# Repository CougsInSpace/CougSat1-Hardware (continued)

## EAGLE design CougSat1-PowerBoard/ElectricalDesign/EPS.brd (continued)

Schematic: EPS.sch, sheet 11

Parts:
C16, C26, C90: 10µF 10%; 1608
C18, C19, C21, C23, C27, C31, C83, C86, C87: 100nF 10%; 1608
RN6, RN7, RN8, RN9, RN10, RN11, RN13, RN14, RN17, RN20, RN21, RN22, RN23: 5kΩ 0.1%; 1616
TP4, TP27, TP28, TP30: TEST_POINT-SMD-C-1.25; SMD-C-1.25
U8, U11, U42: AD7689; QFN-20-4040

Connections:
3.3V: C18.1, C31.1, C87.1, RN14.2 (B1), U8.15 (VIO), U11.15 (VIO), U42.15 (VIO); also elsewhere on the board
ADC_3.3V: RN14.3 (B2), RN14.4 (A2), U8.6 (IN4)
ADC_EJECT_TIMER_BUF: RN13.3 (B2), RN13.4 (A2), U11.19 (IN3)
ADC_PV_IN-0A: RN23.3 (B2), RN23.4 (A2), U42.16 (IN0)
ADC_PV_IN-0B: RN22.3 (B2), RN22.4 (A2), U42.17 (IN1)
ADC_PV_IN-1A: RN21.3 (B2), RN21.4 (A2), U42.18 (IN2)
ADC_PV_IN-1B: RN20.3 (B2), RN20.4 (A2), U42.19 (IN3)
ADC_PV_IN-2A: RN8.3 (B2), RN8.4 (A2), U8.18 (IN2)
ADC_PV_IN-2B: RN9.3 (B2), RN9.4 (A2), U8.19 (IN3)
ADC_PV_IN-3A: RN7.3 (B2), RN7.4 (A2), U8.17 (IN1)
ADC_PV_IN-3B: RN6.3 (B2), RN6.4 (A2), U8.16 (IN0)
ADC_REF-0: C16.1, TP30.1, U8.2 (REF)
ADC_REF-1: C90.1, TP4.1, U42.2 (REF)
ADC_REF-2: C26.1, TP27.1, U11.2 (REF)
ADC_REFIN-0: C21.1, U8.3 (REFIN)
ADC_REFIN-1: C83.1, U42.3 (REFIN)
ADC_REFIN-2: C23.1, U11.3 (REFIN)
ADC_SEL-0: U8.11 (CNV); also elsewhere on the board
ADC_SEL-1: U42.11 (CNV); also elsewhere on the board
ADC_SEL-2: U11.11 (CNV); also elsewhere on the board
ADC_UMB_IN: RN10.3 (B2), RN10.4 (A2), U11.8 (IN6)
ADC_VBATT-A: RN17.3 (B2), RN17.4 (A2), U42.9 (IN7)
ADC_VBATT-B: RN11.3 (B2), RN11.4 (A2), U11.9 (IN7)
AGND: C16.2, C21.2, C23.2, C26.2, C83.2, C90.2, RN6.1 (A1), RN7.1 (A1), RN8.1 (A1), RN9.1 (A1), RN10.1 (A1), RN11.1 (A1), RN13.1 (A1), RN14.1 (A1), RN17.1 (A1), RN20.1 (A1), RN21.1 (A1), RN22.1 (A1), RN23.1 (A1), TP28.1, U8.9 (IN7), U8.10 (COM), U11.10 (COM), U42.10 (COM); also elsewhere on the board
AVDD: C19.1, C27.1, C86.1, U8.1 (VDD), U8.20 (VDD), U11.1 (VDD), U11.20 (VDD), U42.1 (VDD), U42.20 (VDD); also elsewhere on the board
DEPLOY_SENSE-0: U42.8 (IN6); also elsewhere on the board
DGND: C18.2, C19.2, C27.2, C31.2, C86.2, C87.2, U8.4 (GND), U8.5 (GND), U8.PAD (GND), U11.4 (GND), U11.5 (GND), U11.16 (IN0), U11.17 (IN1), U11.18 (IN2), U11.PAD (GND), U42.4 (GND), U42.5 (GND), U42.PAD (GND); also elsewhere on the board
EJECT_TIMER_BUF: RN13.2 (B1); also elsewhere on the board
I_3.3V_IN: U8.8 (IN6); also elsewhere on the board
I_3.3V_OUT: U8.7 (IN5); also elsewhere on the board
I_BATT_IN-A: U42.7 (IN5); also elsewhere on the board
I_BATT_IN-B: U11.6 (IN4); also elsewhere on the board
I_BATT_OUT-A: U42.6 (IN4); also elsewhere on the board
I_BATT_OUT-B: U11.7 (IN5); also elsewhere on the board
PV_IN-0A: RN23.2 (B1); also elsewhere on the board
PV_IN-0B: RN22.2 (B1); also elsewhere on the board
PV_IN-1A: RN21.2 (B1); also elsewhere on the board
PV_IN-1B: RN20.2 (B1); also elsewhere on the board
PV_IN-2A: RN8.2 (B1); also elsewhere on the board
PV_IN-2B: RN9.2 (B1); also elsewhere on the board
PV_IN-3A: RN7.2 (B1); also elsewhere on the board
PV_IN-3B: RN6.2 (B1); also elsewhere on the board
SPI_MISO: U8.14 (SDO), U11.14 (SDO), U42.14 (SDO); also elsewhere on the board
SPI_MOSI: U8.12 (DIN), U11.12 (DIN), U42.12 (DIN); also elsewhere on the board
SPI_SCK: U8.13 (SCK), U11.13 (SCK), U42.13 (SCK); also elsewhere on the board
UMB_IN: RN10.2 (B1); also elsewhere on the board
VBATT-A: RN17.2 (B1); also elsewhere on the board
VBATT-B: RN11.2 (B1); also elsewhere on the board

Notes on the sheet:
CAD Note: Decoupling
0-2.5V=38µV/LSB 76µV/LSB with -6dB attenuation
4A3>
4A5>
4B5>
4B3>
4A1>
4C5>
5B2>
5B5>
5B6>
5B1>
6B6>
6C5>
6B3>
6D2>
<10A1
10A1>
<10B1
<10D1

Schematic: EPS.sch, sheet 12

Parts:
C6, C15, C57, C69, C93: 1µF 10%; 1608
C7, C8, C11, C13, C17, C22, C37, C55, C59, C65, C72, C92, C96: 100nF 10%; 1608
C10, C14, C61, C75, C104: 10µF 10%; 1608
C40: 4.7µF 10%; 4028-POL
FB1: 1.5kΩ @ 100MHz; 1608
RN4, RN12: 10kΩ 5%; 3264
RT3, RT4, RT7, RT10: 10kΩ 5%; 1608
TP1, TP9, TP10, TP20, TP22, TP31, TP33, TP36, TP38: TEST_POINT-SMD-C-1.25; SMD-C-1.25
U2, U9, U26, U35, U49: AD7291; QFN-20-4040
U4, U7: AD8515; SOT23-5

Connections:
3.3V: C7.1, C22.1, C55.1, C65.1, C92.1, FB1.1, U2.11 (AS0), U2.13 (AS1), U2.16 (VDRIVE), U2.17 (!PD!/!RST), U9.16 (VDRIVE), U9.17 (!PD!/!RST), U26.16 (VDRIVE), U26.17 (!PD!/!RST), U35.16 (VDRIVE), U35.17 (!PD!/!RST), U49.11 (AS0), U49.16 (VDRIVE), U49.17 (!PD!/!RST); also elsewhere on the board
ADC_DCAP-3: C93.1, U49.8 (DCAP)
ADC_DCAP-4: C69.1, U35.8 (DCAP)
ADC_DCAP-5: C57.1, U26.8 (DCAP)
ADC_DCAP-6: C15.1, U9.8 (DCAP)
ADC_DCAP-7: C6.1, U2.8 (DCAP)
ADC_REF-3: C104.1, TP1.1, U49.7 (VREF)
ADC_REF-4: C75.1, TP9.1, U35.7 (VREF)
ADC_REF-5: C61.1, TP10.1, U26.7 (VREF)
ADC_REF-6: C14.1, TP33.1, U7.3 (IN+), U9.7 (VREF)
ADC_REF-7: C10.1, TP38.1, U2.7 (VREF), U4.3 (IN+)
AGND: C8.2, C10.2, C11.2, C13.2, C14.2, C17.2, C37.2, C40.C, RT3.1, RT4.1, RT7.1, RT10.1, TP20.1, U2.6 (AGND), U4.2 (V-), U7.2 (V-), U9.6 (AGND); also elsewhere on the board
AVDD: C8.1, C11.1, C13.1, C17.1, C37.1, C40.A, C59.1, C72.1, C96.1, FB1.2, TP22.1, U2.10 (VDD), U4.5 (V+), U7.5 (V+), U9.10 (VDD), U26.10 (VDD), U35.10 (VDD), U49.10 (VDD); also elsewhere on the board
AVREF-0: RN12.5 (C), RN12.10 (C), TP31.1, U7.1 (OUT), U7.4 (IN-)
AVREF-1: RN4.5 (C), RN4.10 (C), TP36.1, U4.1 (OUT), U4.4 (IN-)
DEPLOY_SENSE-1: U2.18 (IN0); also elsewhere on the board
DGND: C6.2, C7.2, C15.2, C22.2, C55.2, C57.2, C65.2, C69.2, C92.2, C93.2, U2.9 (DGND), U2.PAD (DGND), U9.9 (DGND), U9.11 (AS0), U9.PAD (DGND), U26.4 (IN6), U26.9 (DGND), U26.11 (AS0), U26.13 (AS1), U26.19 (IN1), U26.PAD (DGND), U35.9 (DGND), U35.13 (AS1), U35.PAD (DGND), U49.9 (DGND), U49.13 (AS1), U49.PAD (DGND); also elsewhere on the board
I2C_SCL: U2.15 (SCL), U9.15 (SCL), U26.15 (SCL), U35.15 (SCL), U49.15 (SCL); also elsewhere on the board
I2C_SDA: U2.14 (SDA), U9.14 (SDA), U26.14 (SDA), U35.14 (SDA), U49.14 (SDA); also elsewhere on the board
I_3.3V-0: U49.5 (IN7); also elsewhere on the board
I_3.3V-1: U49.4 (IN6); also elsewhere on the board
I_3.3V-2: U49.3 (IN5); also elsewhere on the board
I_3.3V-3: U49.2 (IN4); also elsewhere on the board
I_3.3V-4: U49.1 (IN3); also elsewhere on the board
I_3.3V-5: U49.20 (IN2); also elsewhere on the board
I_3.3V-6: U49.19 (IN1); also elsewhere on the board
I_3.3V-7: U49.18 (IN0); also elsewhere on the board
I_3.3V-8: U35.5 (IN7); also elsewhere on the board
I_3.3V-9: U35.4 (IN6); also elsewhere on the board
I_3.3V-10: U35.3 (IN5); also elsewhere on the board
I_3.3V-11: U35.2 (IN4); also elsewhere on the board
I_3.3V-12: U35.1 (IN3); also elsewhere on the board
I_3.3V-PV: U2.5 (IN7); also elsewhere on the board
I_BATT-0: U35.20 (IN2); also elsewhere on the board
I_BATT-1: U35.19 (IN1); also elsewhere on the board
I_BATT-2: U35.18 (IN0); also elsewhere on the board
I_BATT-3: U26.3 (IN5); also elsewhere on the board
I_BATT-4: U26.2 (IN4); also elsewhere on the board
I_BATT-5: U26.1 (IN3); also elsewhere on the board
I_BATT-6: U26.20 (IN2); also elsewhere on the board
I_BH-0: U26.18 (IN0); also elsewhere on the board
I_BH-1: U9.18 (IN0); also elsewhere on the board
I_DP-0: U9.3 (IN5); also elsewhere on the board
I_DP-1: U2.20 (IN2); also elsewhere on the board
PGND: C59.2, C61.2, C72.2, C75.2, C96.2, C104.2, U26.5 (IN7), U26.6 (AGND), U35.6 (AGND), U49.6 (AGND); also elsewhere on the board
TEMP-BATT-A: RN4.6 (5), U2.3 (IN5); also elsewhere on the board
TEMP-BATT-B: RN4.3, U2.2 (IN4); also elsewhere on the board
TEMP-IN_SW-0: RN4.8 (7), U2.1 (IN3); also elsewhere on the board
TEMP-IN_SW-1: RN12.6 (5), U9.5 (IN7); also elsewhere on the board
TEMP-OUT_SW-0: RN12.1, U9.19 (IN1); also elsewhere on the board
TEMP-OUT_SW-1: RN4.4, U2.4 (IN6); also elsewhere on the board
TEMP-PCB-0: RN4.9 (8), RT4.2, U2.19 (IN1)
TEMP-PCB-1: RN12.8 (7), RT7.2, U9.2 (IN4)
TEMP-PCB-2: RN12.2, RT10.2, U9.1 (IN3)
TEMP-PCB-3: RN12.4, RT3.2, U9.4 (IN6)
TEMP-REG: RN12.9 (8), U9.20 (IN2); also elsewhere on the board

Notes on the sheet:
CAD Note: Decoupling
Addr=0x2C (7b)
Addr=0x2E (7b)
Addr=0x2F (7b)
Addr=0x2B (7b)
Addr=0x20 (7b)
CAD Note: Place at various locations around the PCB
0-2.5V=610µV/LSB
Note: Inputs PGND Referenced
<10B1
<10B1>
12A4>
7A2>
7A4>
7A6>
7B2>
7B4>
7B6>
7C2>
7C4>
7C6>
7D2>
7D4>
7D6>
8A2>
8A4>
8A6>
8B2>
8B4>
8B6>
8C2>
8C4>
8C6>
8D6>
8D4>
8D2>
4D6>
4D3>
5B2>
5B5>

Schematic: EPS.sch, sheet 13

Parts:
J6: CougSat Card; CARD-FULL-OPEN+X
LOGO1: SIGNATUREBRADLEY; SIGN-BRADLEY
LOGO2: Satellite 16mm; CIS-SATELLITE-16

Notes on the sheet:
PV 0,1
PV 2,3
PV 4,5
PV 6,7
Battery 0
Battery 1
PMIC SWD
Umb
RBF Pin
RBF Switch
Deploy ables

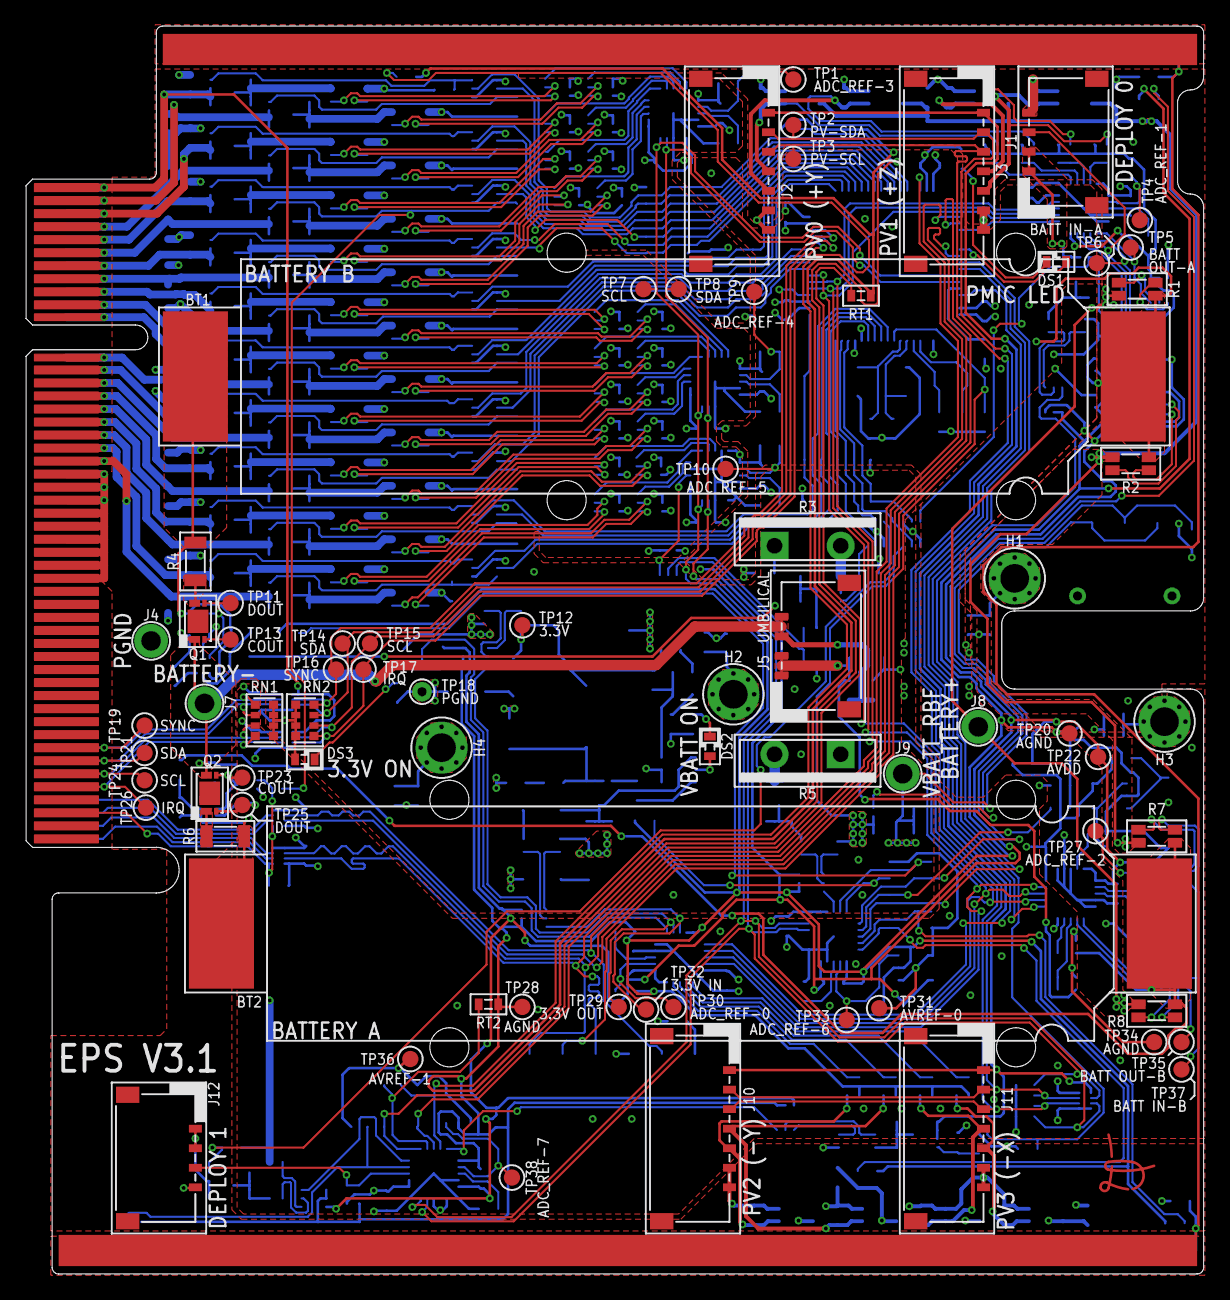
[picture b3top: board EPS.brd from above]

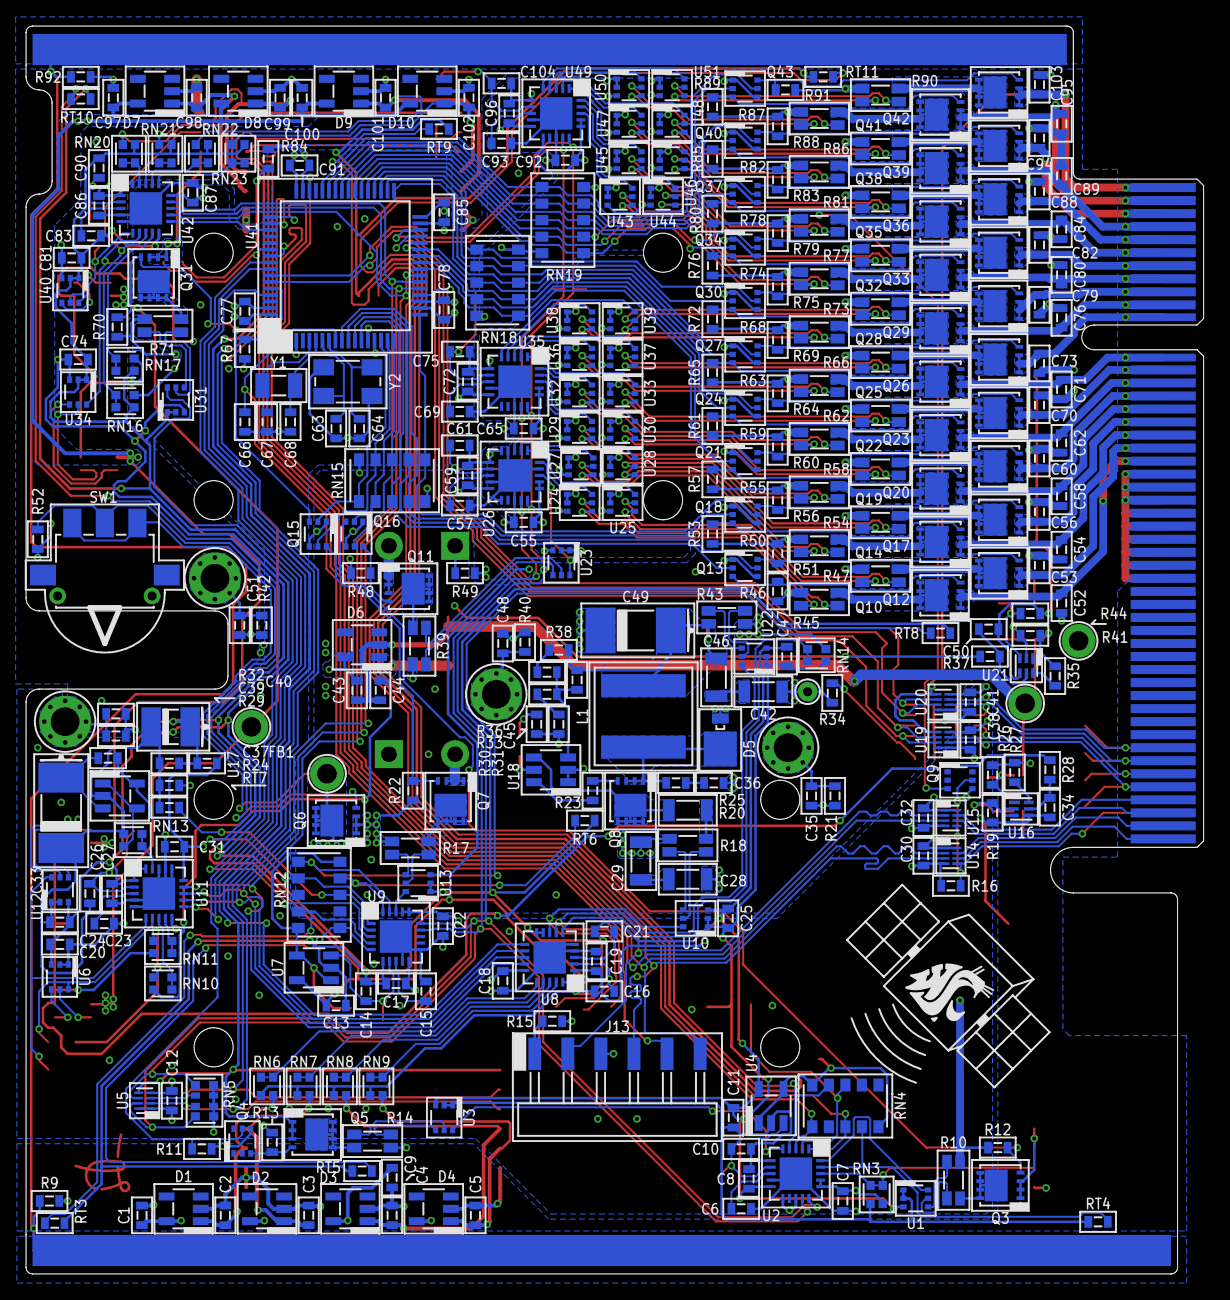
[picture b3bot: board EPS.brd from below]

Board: 4 copper layers, 90.4 x 95.8 mm, 401 parts (327 on the bottom side), 328 nets.

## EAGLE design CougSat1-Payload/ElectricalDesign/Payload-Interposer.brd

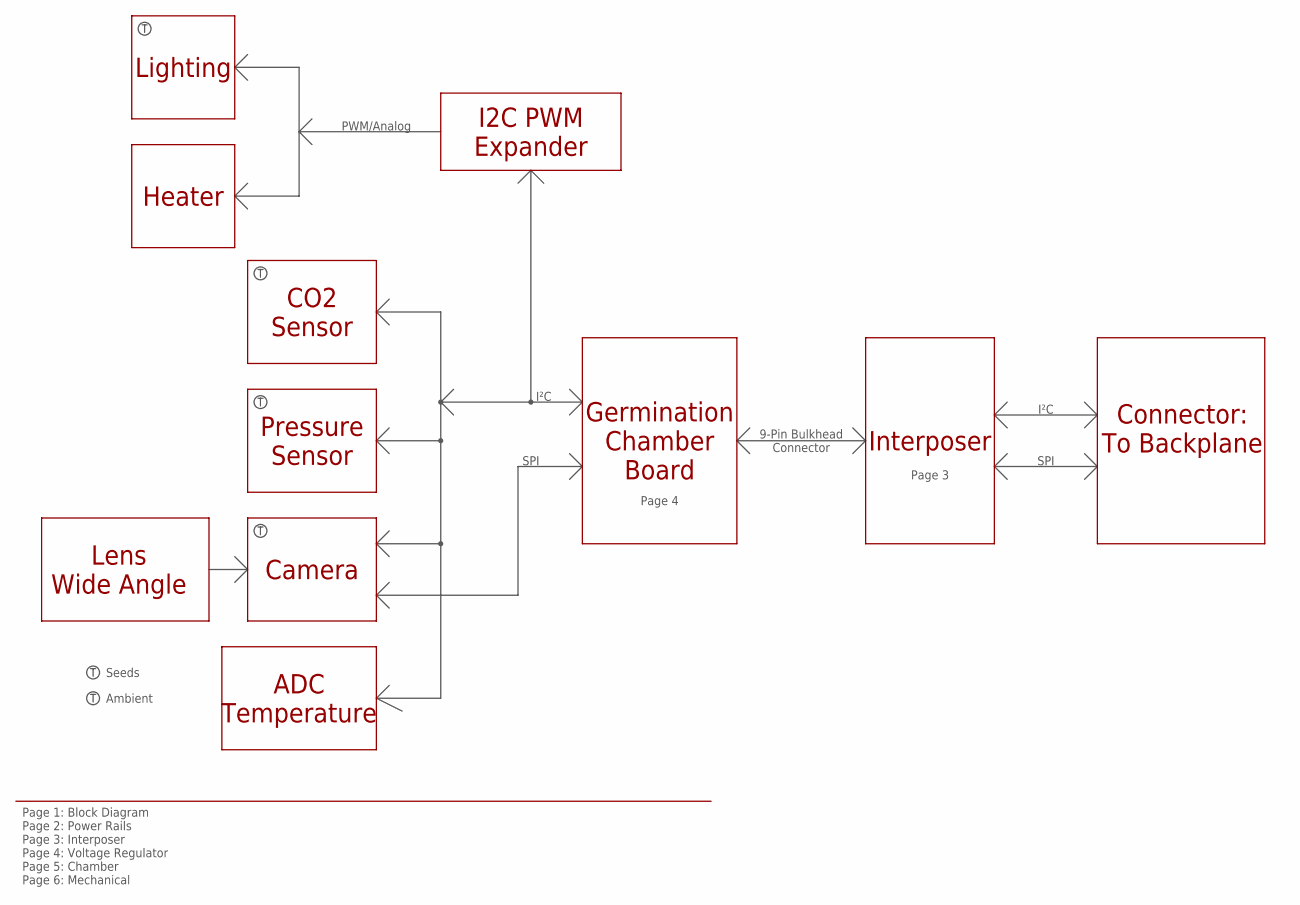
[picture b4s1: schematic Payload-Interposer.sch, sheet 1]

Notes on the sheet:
Connector: To Backplane
Camera
Lighting
Lens Wide Angle
Pressure Sensor
ADC Temperature
I²C
SPI
Seeds
Page 1: Block Diagram Page 2: Power Rails Page 3: Interposer Page 4: Voltage Regulator Page 5: Chamber Page 6: Mechanical
Heater
Ambient
CO2 Sensor
Interposer
Germination Chamber Board
9-Pin Bulkhead Connector
I2C PWM Expander
PWM/Analog
Page 3
Page 4

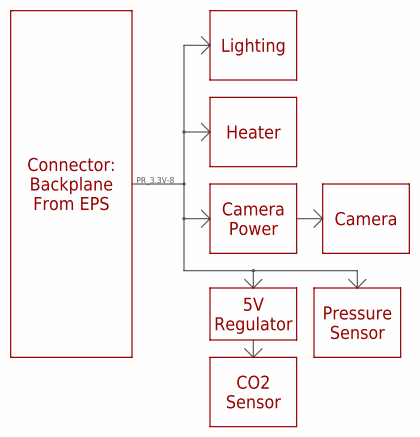
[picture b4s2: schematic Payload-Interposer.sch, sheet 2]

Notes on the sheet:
Connector: Backplane From EPS
Camera Power
Heater
CO2 Sensor
Pressure Sensor
PR_3.3V-8
Lighting
5V Regulator
Camera

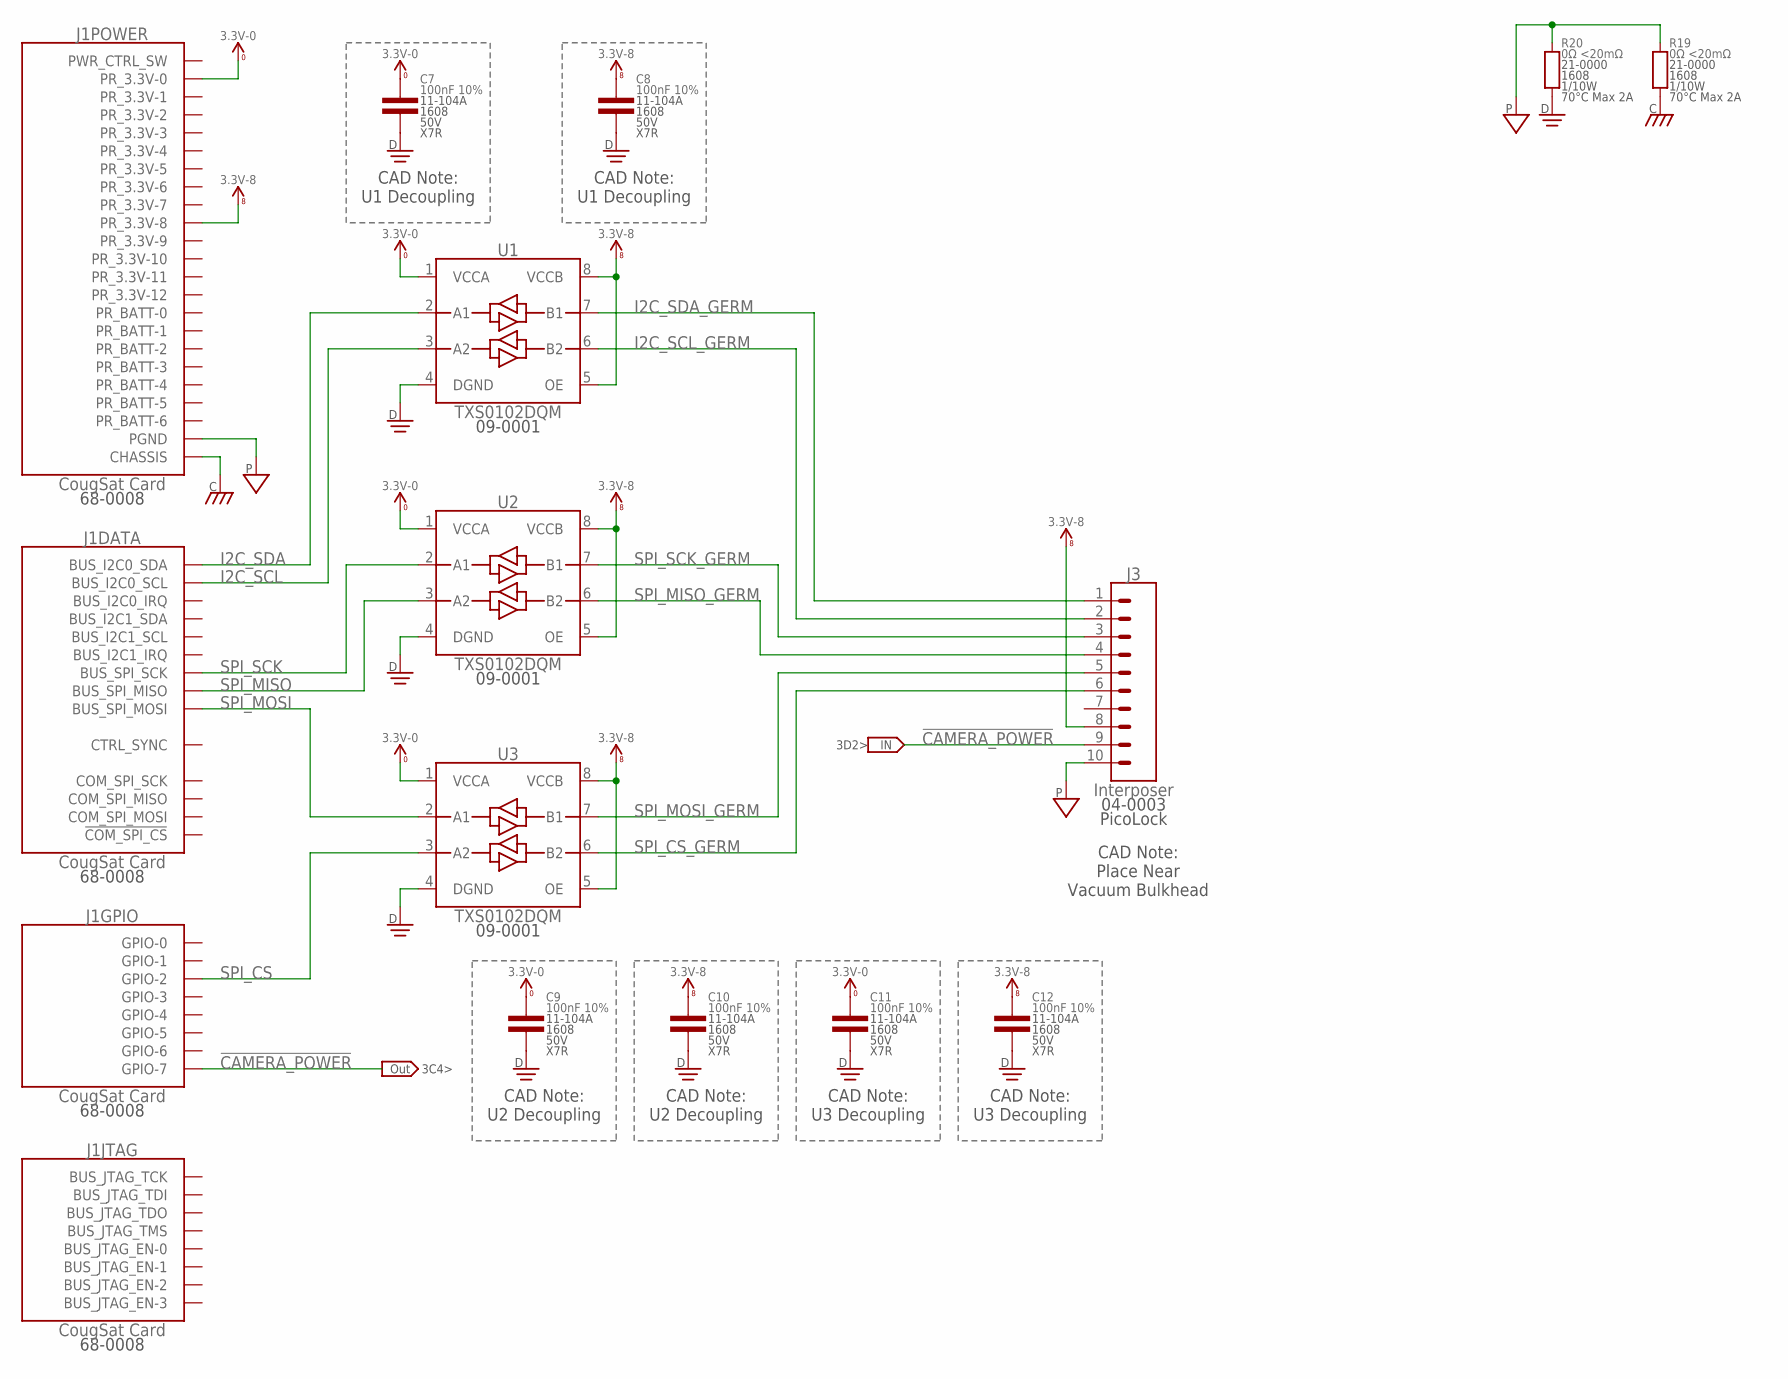
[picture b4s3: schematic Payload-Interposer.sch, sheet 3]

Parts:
C7, C8, C9, C10, C11, C12: 100nF 10%; 1608
J1: CougSat Card; CARD-FULL-OPEN+X
J3: Interposer; PICOLOCK1.5-10
R19, R20: 0Ω <20mΩ; 1608
U1, U2, U3: TXS0102DQM; X2SON-8

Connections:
3.3V_0: C7.1, C9.1, C11.1, J1.A1 (PR_3.3V-0), J1.B1 (PR_3.3V-0), U1.1 (VCCA), U2.1 (VCCA), U3.1 (VCCA)
3.3V_8: C8.1, C10.1, C12.1, J1.A9 (PR_3.3V-8), J1.B9 (PR_3.3V-8), J3.8, U1.5 (OE), U1.8 (VCCB), U2.5 (OE), U2.8 (VCCB), U3.5 (OE), U3.8 (VCCB); also elsewhere on the board
!CAMERA_POWER: J1.B41 (GPIO-7), J3.9; also elsewhere on the board
CHASSIS: J1.CHASSIS@1 (CHASSIS), J1.CHASSIS@2 (CHASSIS), J1.CHASSIS@3 (CHASSIS), J1.CHASSIS@4 (CHASSIS), R19.1; also elsewhere on the board
DGND: C7.2, C8.2, C9.2, C10.2, C11.2, C12.2, R20.1, U1.4 (DGND), U2.4 (DGND), U3.4 (DGND); also elsewhere on the board
I2C_SCL: J1.A44 (BUS_I2C0_SCL), J1.B44 (BUS_I2C0_SCL), U1.3 (A2)
I2C_SCL_GERM: J3.2, U1.6 (B2); also elsewhere on the board
I2C_SDA: J1.A43 (BUS_I2C0_SDA), J1.B43 (BUS_I2C0_SDA), U1.2 (A1)
I2C_SDA_GERM: J3.1, U1.7 (B1); also elsewhere on the board
PGND: J1.A21 (PGND), J1.A22 (PGND), J1.A23 (PGND), J1.B21 (PGND), J1.B22 (PGND), J1.B23 (PGND), J1.B24 (PGND), J1.B25 (PGND), J1.B26 (PGND), J1.B27 (PGND), J1.B28 (PGND), J1.B29 (PGND), J3.10, R19.2, R20.2; also elsewhere on the board
PR_3.3V-1: J1.A2 (PR_3.3V-1), J1.B2 (PR_3.3V-1)
PR_3.3V-2: J1.A3 (PR_3.3V-2), J1.B3 (PR_3.3V-2)
PR_3.3V-3: J1.A4 (PR_3.3V-3), J1.B4 (PR_3.3V-3)
PR_3.3V-4: J1.A5 (PR_3.3V-4), J1.B5 (PR_3.3V-4)
PR_3.3V-5: J1.A6 (PR_3.3V-5), J1.B6 (PR_3.3V-5)
PR_3.3V-6: J1.A7 (PR_3.3V-6), J1.B7 (PR_3.3V-6)
PR_3.3V-7: J1.A8 (PR_3.3V-7), J1.B8 (PR_3.3V-7)
PR_3.3V-9: J1.A10 (PR_3.3V-9), J1.B10 (PR_3.3V-9)
PR_3.3V-10: J1.A11 (PR_3.3V-10), J1.B11 (PR_3.3V-10)
PR_3.3V-11: J1.A12 (PR_3.3V-11), J1.B12 (PR_3.3V-11)
PR_3.3V-12: J1.A13 (PR_3.3V-12), J1.B13 (PR_3.3V-12)
PR_BATT-0: J1.A14 (PR_BATT-0), J1.B14 (PR_BATT-0)
PR_BATT-1: J1.A15 (PR_BATT-1), J1.B15 (PR_BATT-1)
PR_BATT-2: J1.A16 (PR_BATT-2), J1.B16 (PR_BATT-2)
PR_BATT-3: J1.A17 (PR_BATT-3), J1.B17 (PR_BATT-3)
PR_BATT-4: J1.A18 (PR_BATT-4), J1.B18 (PR_BATT-4)
PR_BATT-5: J1.A19 (PR_BATT-5), J1.B19 (PR_BATT-5)
PR_BATT-6: J1.A20 (PR_BATT-6), J1.B20 (PR_BATT-6)
SPI_CS: J1.A26 (GPIO-2), U3.3 (A2)
SPI_CS_GERM: J3.6, U3.6 (B2); also elsewhere on the board
SPI_MISO: J1.A38 (BUS_SPI_MISO), J1.B38 (BUS_SPI_MISO), U2.3 (A2)
SPI_MISO_GERM: J3.4, U2.6 (B2); also elsewhere on the board
SPI_MOSI: J1.A39 (BUS_SPI_MOSI), J1.B39 (BUS_SPI_MOSI), U3.2 (A1)
SPI_MOSI_GERM: J3.5, U3.7 (B1); also elsewhere on the board
SPI_SCK: J1.A37 (BUS_SPI_SCK), J1.B37 (BUS_SPI_SCK), U2.2 (A1)
SPI_SCK_GERM: J3.3, U2.7 (B1); also elsewhere on the board

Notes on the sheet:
CAD Note: Place Near Vacuum Bulkhead
CAD Note: U1 Decoupling
CAD Note: U2 Decoupling
CAD Note: U3 Decoupling
3C4>
3D2>

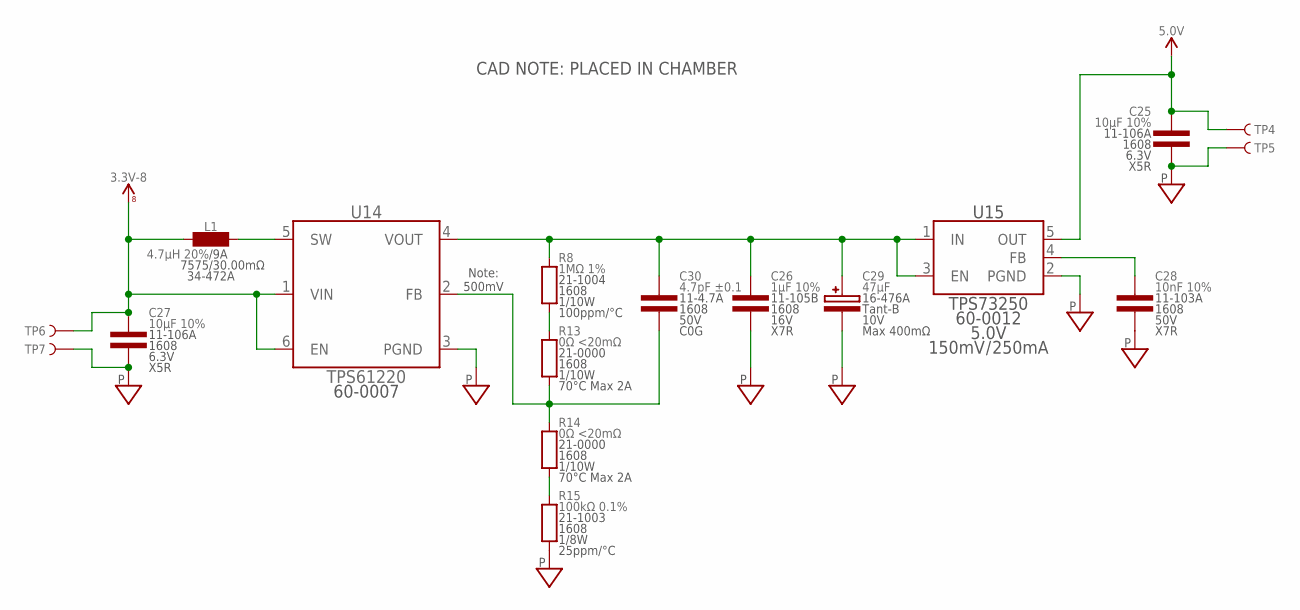
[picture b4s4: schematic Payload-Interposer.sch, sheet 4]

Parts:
C25, C27: 10µF 10%; 1608
C26: 1µF 10%; 1608
C28: 10nF 10%; 1608
C29: 47µF; 4028-POL
C30: 4.7pF ±0.1; 1608
L1: 4.7µH 20%; 7575
R8: 1MΩ 1%; 1608
R13, R14: 0Ω <20mΩ; 1608
R15: 100kΩ 0.1%; 1608
TP4, TP5, TP6, TP7: TEST_POINT-THT-1.0; THT-1.0
U14: TPS61220; SOT363
U15: TPS73250; SOT23-5

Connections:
3.3V_8: C27.1, L1.1, TP6.1, U14.1 (VIN), U14.6 (EN); also elsewhere on the board
5.0V: C25.1, TP4.1, U15.5 (OUT); also elsewhere on the board
BOOST_FB: C30.2, R13.1, R14.2, U14.2 (FB)
BOOST_FB-HIGH: R8.1, R13.2
BOOST_FB-LOW: R14.1, R15.2
BOOST_IN: L1.2, U14.5 (SW)
BOOST_OUT: C26.1, C29.A, C30.1, R8.2, U14.4 (VOUT), U15.1 (IN), U15.3 (EN)
PGND: C25.2, C26.2, C27.2, C28.2, C29.C, R15.1, TP5.1, TP7.1, U14.3 (PGND), U15.2 (PGND); also elsewhere on the board
REG_FB: C28.1, U15.4 (FB)

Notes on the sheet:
Note: 500mV
CAD NOTE: PLACED IN CHAMBER

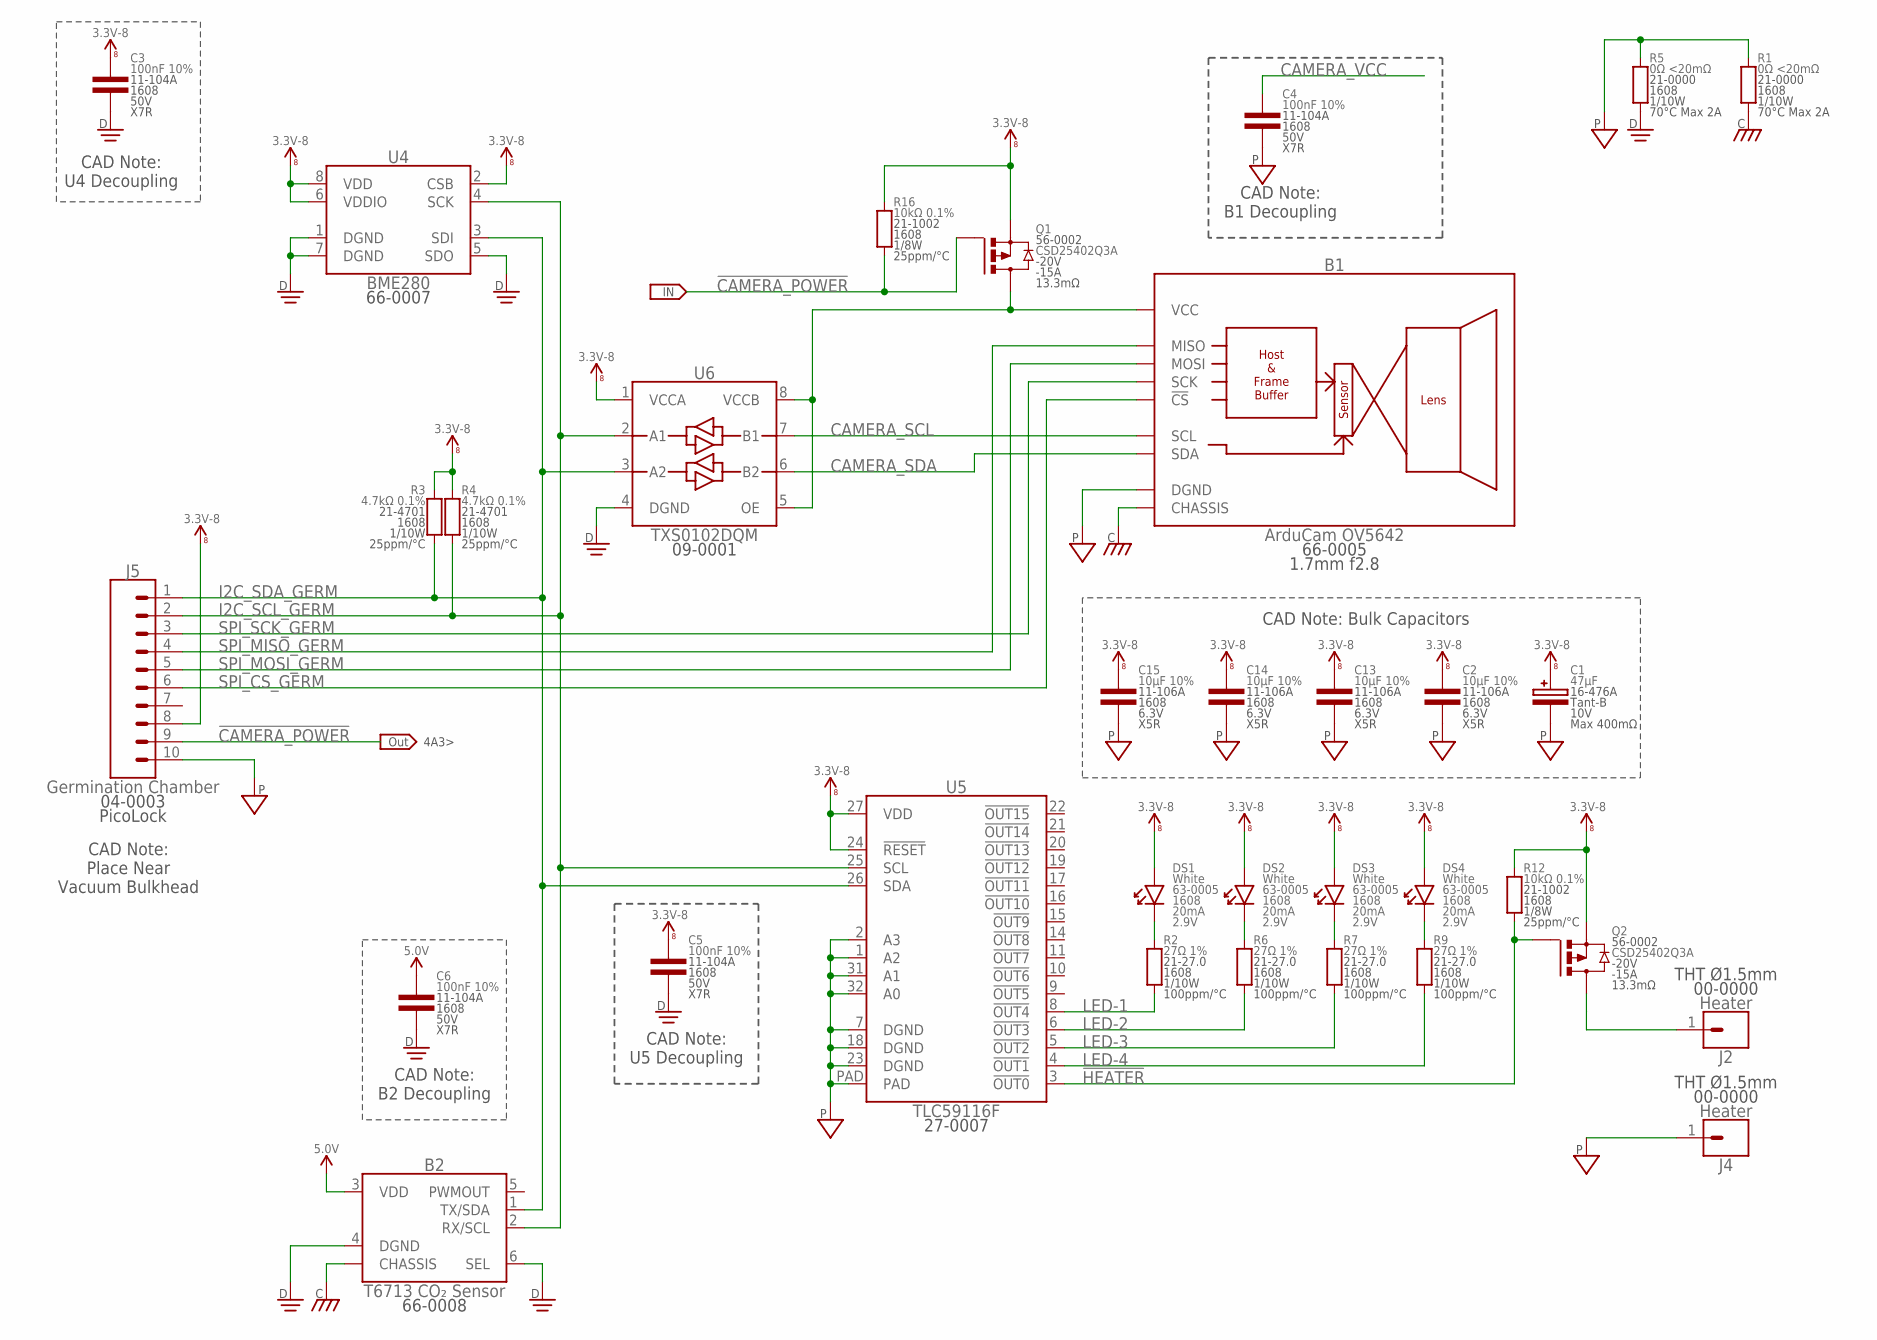
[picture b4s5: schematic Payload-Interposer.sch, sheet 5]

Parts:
B1: ArduCam OV5642; ARDUCAM
B2: T6713 CO₂ Sensor; T6713
C1: 47µF; 4028-POL
C2, C13, C14, C15: 10µF 10%; 1608
C3, C4, C5, C6: 100nF 10%; 1608
DS1, DS2, DS3, DS4: White; 1608-POL
J2, J4: Heater; THT-1.5
J5: Germination Chamber; PICOLOCK1.5-10
Q1, Q2: CSD25402Q3A; SON-3333
R1, R5: 0Ω <20mΩ; 1608
R2, R6, R7, R9: 27Ω 1%; 1608
R3, R4: 4.7kΩ 0.1%; 1608
R12, R16: 10kΩ 0.1%; 1608
U4: BME280
U5: TLC59116F; QFN-32-5050
U6: TXS0102DQM; X2SON-8

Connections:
3.3V_8: C1.A, C2.1, C3.1, C5.1, C13.1, C14.1, C15.1, DS1.A, DS2.A, DS3.A, DS4.A, J5.8, Q1.5 (S), Q1.6 (S), Q1.7 (S), Q1.8 (S), Q1.PAD (S), Q2.5 (S), Q2.6 (S), Q2.7 (S), Q2.8 (S), Q2.PAD (S), R3.2, R4.2, R12.2, R16.2, U4.2 (CSB), U4.6 (VDDIO), U4.8 (VDD), U5.24 (!RESET), U5.27 (VDD), U6.1 (VCCA); also elsewhere on the board
5.0V: B2.3 (VDD), C6.1; also elsewhere on the board
!CAMERA_POWER: J5.9, Q1.4 (G), R16.1; also elsewhere on the board
!HEATER: Q2.4 (G), R12.1, U5.3 (!OUT0)
CAMERA_SCL: B1.8 (SCL), U6.7 (B1)
CAMERA_SDA: B1.7 (SDA), U6.6 (B2)
CAMERA_VCC: B1.6 (VCC), C4.1, Q1.1 (D), Q1.2 (D), Q1.3 (D), U6.5 (OE), U6.8 (VCCB)
CHASSIS: B1.CHASSIS@1 (CHASSIS), B1.CHASSIS@2 (CHASSIS), B1.CHASSIS@3 (CHASSIS), B1.CHASSIS@4 (CHASSIS), B1.CHASSIS@5 (CHASSIS), B1.CHASSIS@6 (CHASSIS), B1.CHASSIS@7 (CHASSIS), B1.CHASSIS@8 (CHASSIS), B1.CHASSIS@9 (CHASSIS), B1.CHASSIS@10 (CHASSIS), B1.CHASSIS@11 (CHASSIS), B1.CHASSIS@12 (CHASSIS), B1.CHASSIS@13 (CHASSIS), B1.CHASSIS@14 (CHASSIS), B1.CHASSIS@15 (CHASSIS), B1.CHASSIS@16 (CHASSIS), B1.CHASSIS@17 (CHASSIS), B1.CHASSIS@18 (CHASSIS), B2.CHASSIS@1 (CHASSIS), B2.CHASSIS@2 (CHASSIS), R1.1; also elsewhere on the board
DGND: B2.4 (DGND), B2.6 (SEL), C3.2, C5.2, C6.2, R5.1, U4.1 (DGND), U4.5 (SDO), U4.7 (DGND), U6.4 (DGND); also elsewhere on the board
HEATER_SOURCE: J2.1, Q2.1 (D), Q2.2 (D), Q2.3 (D)
I2C_SCL_GERM: B2.2 (RX/SCL), J5.2, R4.1, U4.4 (SCK), U5.25 (SCL), U6.2 (A1); also elsewhere on the board
I2C_SDA_GERM: B2.1 (TX/SDA), J5.1, R3.1, U4.3 (SDI), U5.26 (SDA), U6.3 (A2); also elsewhere on the board
LED-1: R2.1, U5.8 (!OUT4)
LED-2: R6.1, U5.6 (!OUT3)
LED-3: R7.1, U5.5 (!OUT2)
LED-4: R9.1, U5.4 (!OUT1)
LED_1_INT: DS1.C, R2.2
LED_2_INT: DS2.C, R6.2
LED_3_INT: DS3.C, R7.2
LED_4_INT: DS4.C, R9.2
PGND: B1.5 (DGND), C1.C, C2.2, C4.2, C13.2, C14.2, C15.2, J4.1, J5.10, R1.2, R5.2, U5.1 (A2), U5.2 (A3), U5.7 (DGND), U5.18 (DGND), U5.23 (DGND), U5.31 (A1), U5.32 (A0), U5.PAD; also elsewhere on the board
SPI_CS_GERM: B1.1 (!CS), J5.6; also elsewhere on the board
SPI_MISO_GERM: B1.3 (MISO), J5.4; also elsewhere on the board
SPI_MOSI_GERM: B1.2 (MOSI), J5.5; also elsewhere on the board
SPI_SCK_GERM: B1.4 (SCK), J5.3; also elsewhere on the board

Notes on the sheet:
CAD Note: U4 Decoupling
CAD Note: B2 Decoupling
CAD Note: B1 Decoupling
CAD Note: U5 Decoupling
CAD Note: Place Near Vacuum Bulkhead
4A3>
>4B2
CAD Note: Bulk Capacitors

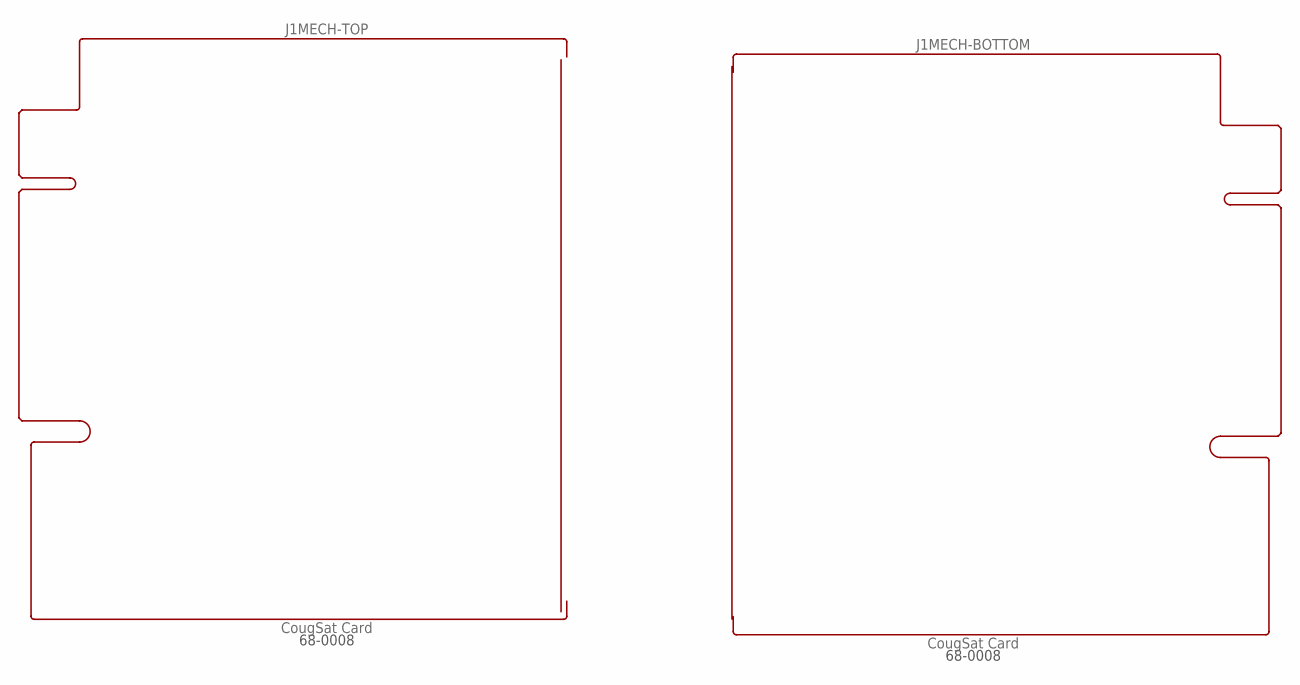
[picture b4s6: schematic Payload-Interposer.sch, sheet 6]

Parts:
J1: CougSat Card; CARD-FULL-OPEN+X

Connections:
PR_3.3V-1: J1.A2 (PR_3.3V-1), J1.B2 (PR_3.3V-1)
PR_3.3V-2: J1.A3 (PR_3.3V-2), J1.B3 (PR_3.3V-2)
PR_3.3V-3: J1.A4 (PR_3.3V-3), J1.B4 (PR_3.3V-3)
PR_3.3V-4: J1.A5 (PR_3.3V-4), J1.B5 (PR_3.3V-4)
PR_3.3V-5: J1.A6 (PR_3.3V-5), J1.B6 (PR_3.3V-5)
PR_3.3V-6: J1.A7 (PR_3.3V-6), J1.B7 (PR_3.3V-6)
PR_3.3V-7: J1.A8 (PR_3.3V-7), J1.B8 (PR_3.3V-7)
PR_3.3V-9: J1.A10 (PR_3.3V-9), J1.B10 (PR_3.3V-9)
PR_3.3V-10: J1.A11 (PR_3.3V-10), J1.B11 (PR_3.3V-10)
PR_3.3V-11: J1.A12 (PR_3.3V-11), J1.B12 (PR_3.3V-11)
PR_3.3V-12: J1.A13 (PR_3.3V-12), J1.B13 (PR_3.3V-12)
PR_BATT-0: J1.A14 (PR_BATT-0), J1.B14 (PR_BATT-0)
PR_BATT-1: J1.A15 (PR_BATT-1), J1.B15 (PR_BATT-1)
PR_BATT-2: J1.A16 (PR_BATT-2), J1.B16 (PR_BATT-2)
PR_BATT-3: J1.A17 (PR_BATT-3), J1.B17 (PR_BATT-3)
PR_BATT-4: J1.A18 (PR_BATT-4), J1.B18 (PR_BATT-4)
PR_BATT-5: J1.A19 (PR_BATT-5), J1.B19 (PR_BATT-5)
PR_BATT-6: J1.A20 (PR_BATT-6), J1.B20 (PR_BATT-6)

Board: 2 copper layers, 63 parts (0 on the bottom side), 56 nets, no tracks yet.

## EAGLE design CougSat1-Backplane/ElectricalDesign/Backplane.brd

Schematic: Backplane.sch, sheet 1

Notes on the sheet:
Slot 0
Slot 1
Slot 2
Slot 3
Slot 4
Page 1: Block Diagram Page 2: Data Bus Slots 0 - 3 Page 3: Data Bus Slots 4 - 7 Page 4: Power Bus Page 5: Mechanical
Page 2, 4
Page 3, 4
Power, Data
